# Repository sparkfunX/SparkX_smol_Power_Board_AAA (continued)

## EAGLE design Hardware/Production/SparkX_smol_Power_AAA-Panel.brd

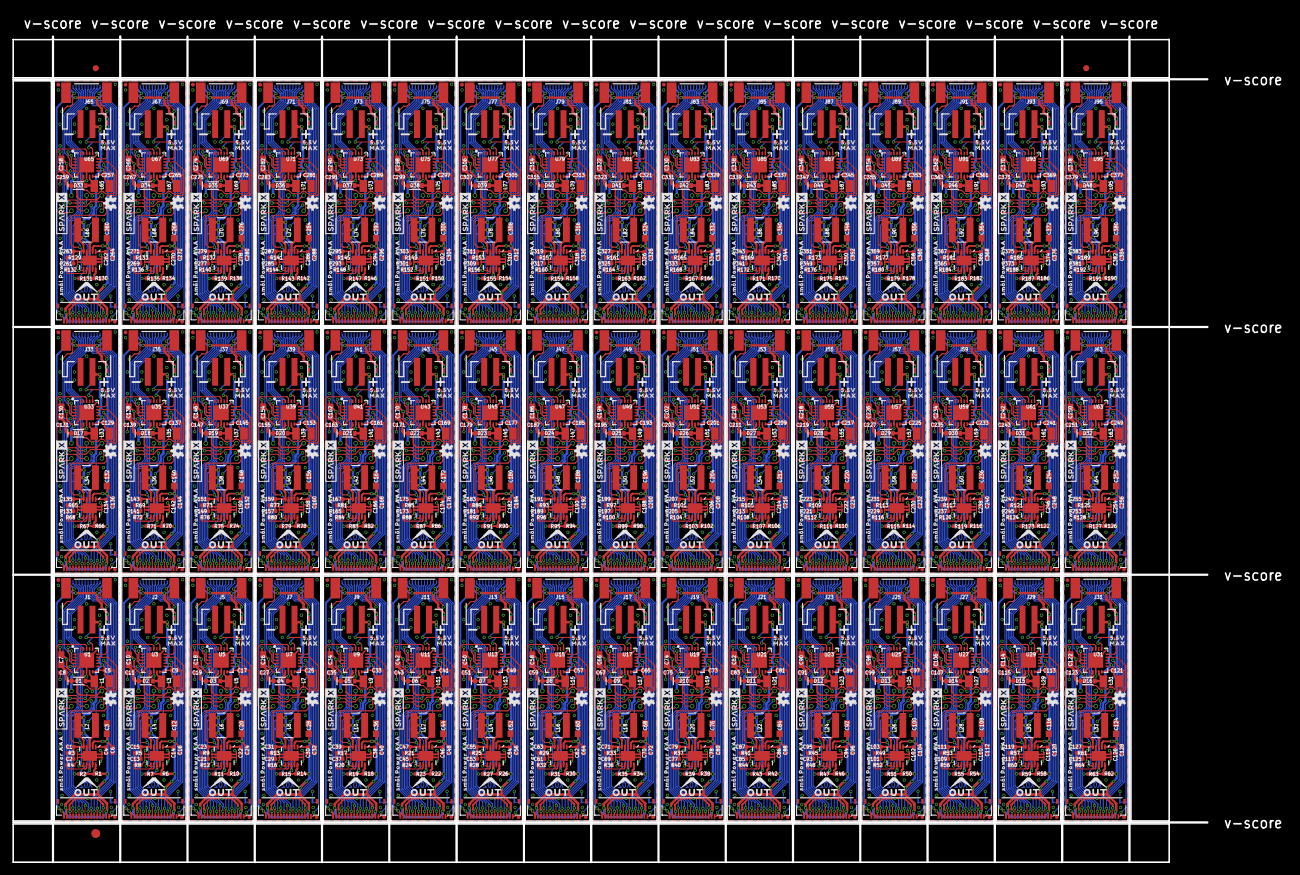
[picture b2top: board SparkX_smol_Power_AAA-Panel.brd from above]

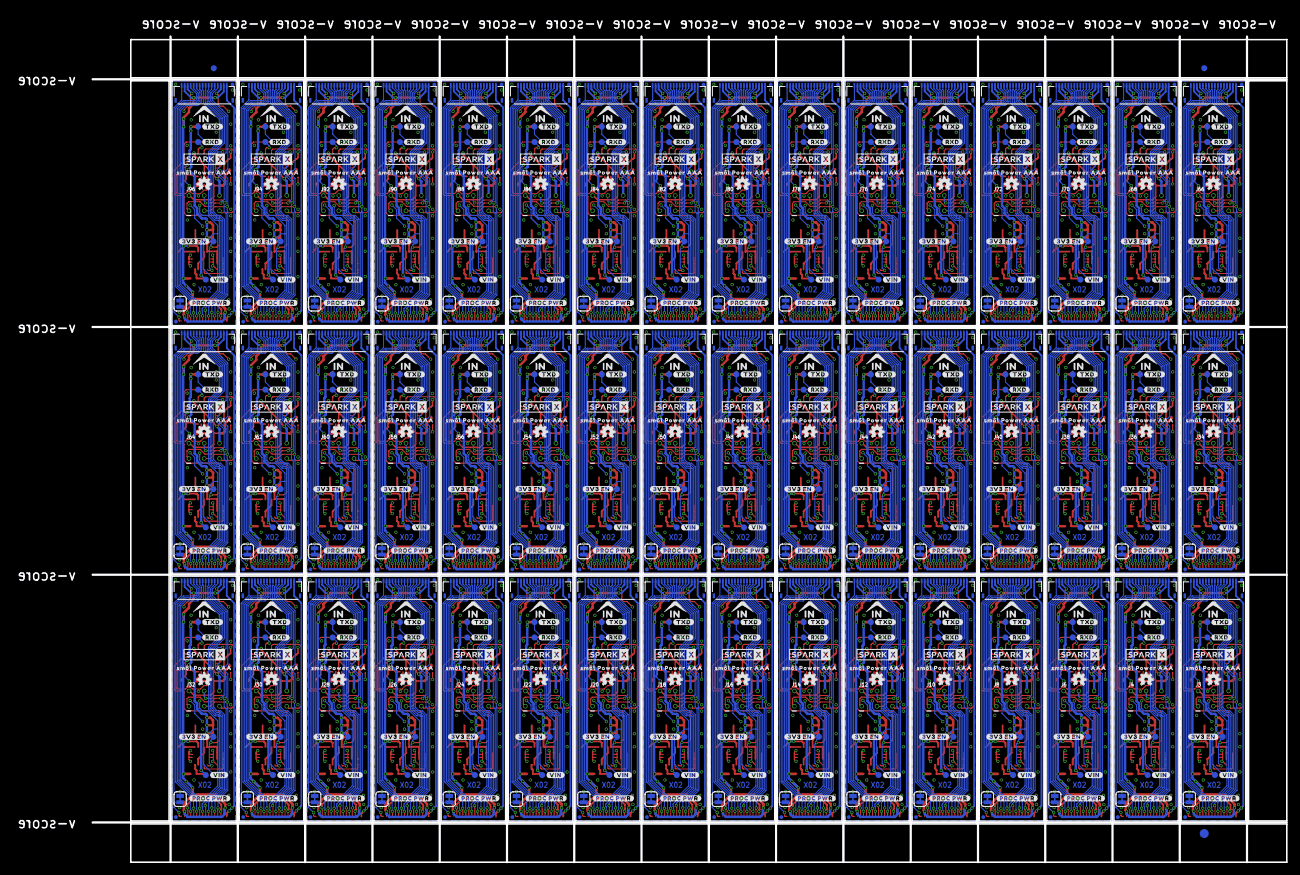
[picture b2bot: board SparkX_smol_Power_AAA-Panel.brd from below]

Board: 2 copper layers, 198.4 x 137.2 mm, 2262 parts (915 on the bottom side), 1248 nets.

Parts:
3V3_EN, 3V3_EN1, 3V3_EN2, 3V3_EN3, 3V3_EN4, 3V3_EN5, 3V3_EN6, 3V3_EN7, 3V3_EN8, 3V3_EN9, 3V3_EN10, 3V3_EN11, 3V3_EN12, 3V3_EN13, 3V3_EN14, 3V3_EN15, 3V3_EN16, 3V3_EN17, 3V3_EN18, 3V3_EN19, 3V3_EN20, 3V3_EN21, 3V3_EN22, 3V3_EN23, 3V3_EN24, 3V3_EN25, 3V3_EN26, 3V3_EN27, 3V3_EN28, 3V3_EN29, 3V3_EN30, 3V3_EN31, 3V3_EN32, 3V3_EN33, 3V3_EN34, 3V3_EN35, 3V3_EN36, 3V3_EN37, 3V3_EN38, 3V3_EN39, 3V3_EN40, 3V3_EN41, 3V3_EN42, 3V3_EN43, 3V3_EN44, 3V3_EN45, 3V3_EN46, 3V3_EN47: TEST-POINT3X4; PAD.03X.04
C1, C15, C23, C31, C39, C47, C55, C63, C71, C79, C87, C95, C103, C111, C119, C127, C135, C143, C151, C159, C167, C175, C183, C191, C199, C207, C215, C223, C231, C239, C247, C255, C263, C271, C279, C287, C295, C303, C311, C319, C327, C335, C343, C351, C359, C367, C375, C383: 10uF; 0402-TIGHT
C2, C4, C6, C8, C11, C13, C14, C16, C19, C21, C22, C24, C27, C29, C30, C32, C35, C37, C38, C40, C43, C45, C46, C48, C51, C53, C54, C56, C59, C61, C62, C64, C67, C69, C70, C72, C75, C77, C78, C80, C83, C85, C86, C88, C91, C93, C94, C96, C99, C101, C102, C104, C107, C109, C110, C112, C115, C117, C118, C120, C123, C125, C126, C128, C131, C133, C134, C136, C139, C141, C142, C144, C147, C149, C150, C152, C155, C157, C158, C160, C163, C165, C166, C168, C171, C173, C174, C176, C179, C181, C182, C184, C187, C189, C190, C192, C195, C197, C198, C200, C203, C205, C206, C208, C211, C213, C214, C216, C219, C221, C222, C224, C227, C229, C230, C232, C235, C237, C238, C240, C243, C245, C246, C248, C251, C253, C254, C256, C259, C261, C262, C264, C267, C269, C270, C272, C275, C277, C278, C280, C283, C285, C286, C288, C291, C293, C294, C296, C299, C301, C302, C304, C307, C309, C310, C312, C315, C317, C318, C320, C323, C325, C326, C328, C331, C333, C334, C336, C339, C341, C342, C344, C347, C349, C350, C352, C355, C357, C358, C360, C363, C365, C366, C368, C371, C373, C374, C376, C379, C381, C382, C384: 0.1uF; 0402-TIGHT
C3, C7, C10, C12, C18, C20, C26, C28, C34, C36, C42, C44, C50, C52, C58, C60, C66, C68, C74, C76, C82, C84, C90, C92, C98, C100, C106, C108, C114, C116, C122, C124, C130, C132, C138, C140, C146, C148, C154, C156, C162, C164, C170, C172, C178, C180, C186, C188, C194, C196, C202, C204, C210, C212, C218, C220, C226, C228, C234, C236, C242, C244, C250, C252, C258, C260, C266, C268, C274, C276, C282, C284, C290, C292, C298, C300, C306, C308, C314, C316, C322, C324, C330, C332, C338, C340, C346, C348, C354, C356, C362, C364, C370, C372, C378, C380: 22uF; 0603
C5, C9, C17, C25, C33, C41, C49, C57, C65, C73, C81, C89, C97, C105, C113, C121, C129, C137, C145, C153, C161, C169, C177, C185, C193, C201, C209, C217, C225, C233, C241, C249, C257, C265, C273, C281, C289, C297, C305, C313, C321, C329, C337, C345, C353, C361, C369, C377: 4.7uF; 0402-TIGHT
D1, D2, D3, D4, D5, D6, D7, D8, D9, D10, D11, D12, D13, D14, D15, D16, D17, D18, D19, D20, D21, D22, D23, D24, D25, D26, D27, D28, D29, D30, D31, D32, D33, D34, D35, D36, D37, D38, D39, D40, D41, D42, D43, D44, D45, D46, D47, D48: 1A/23V/620mV; SOD-323
E$1, E$2, E$3, E$4: FIDUCIAL-1X2
E$5, E$6: FIDUCIAL-1.5X3
FD1, FD2, FD3, FD4, FD5, FD6, FD7, FD8, FD9, FD10, FD11, FD12, FD13, FD14, FD15, FD16, FD17, FD18, FD19, FD20, FD21, FD22, FD23, FD24, FD25, FD26, FD27, FD28, FD29, FD30, FD31, FD32, FD33, FD34, FD35, FD36, FD37, FD38, FD39, FD40, FD41, FD42, FD43, FD44, FD45, FD46, FD47, FD48, FD49, FD50, FD51, FD52, FD53, FD54, FD55, FD56, FD57, FD58, FD59, FD60, FD61, FD62, FD63, FD64, FD65, FD66, FD67, FD68, FD69, FD70, FD71, FD72, FD73, FD74, FD75, FD76, FD77, FD78, FD79, FD80, FD81, FD82, FD83, FD84, FD85, FD86, FD87, FD88, FD89, FD90, FD91, FD92, FD93, FD94, FD95, FD96, FD97, FD98, FD99, FD100, FD101, FD102, FD103, FD104, FD105, FD106, FD107, FD108, FD109, FD110, FD111, FD112, FD113, FD114, FD115, FD116, FD117, FD118, FD119, FD120, FD121, FD122, FD123, FD124, FD125, FD126, FD127, FD128, FD129, FD130, FD131, FD132, FD133, FD134, FD135, FD136, FD137, FD138, FD139, FD140, FD141, FD142, FD143, FD144, FD145, FD146, FD147, FD148, FD149, FD150, FD151, FD152, FD153, FD154, FD155, FD156, FD157, FD158, FD159, FD160, FD161, FD162, FD163, FD164, FD165, FD166, FD167, FD168, FD169, FD170, FD171, FD172, FD173, FD174, FD175, FD176, FD177, FD178, FD179, FD180, FD181, FD182, FD183, FD184, FD185, FD186, FD187, FD188, FD189, FD190, FD191, FD192: FIDUCIALUFIDUCIAL; FIDUCIAL-MICRO
IN, IN1, IN2, IN3, IN4, IN5, IN6, IN7, IN8, IN9, IN10, IN11, IN12, IN13, IN14, IN15, IN16, IN17, IN18, IN19, IN20, IN21, IN22, IN23, IN24, IN25, IN26, IN27, IN28, IN29, IN30, IN31, IN32, IN33, IN34, IN35, IN36, IN37, IN38, IN39, IN40, IN41, IN42, IN43, IN44, IN45, IN46, IN47: FPC_16_0.5MM
J1, J2, J5, J7, J9, J11, J13, J15, J17, J19, J21, J23, J25, J27, J29, J31, J33, J35, J37, J39, J41, J43, J45, J47, J49, J51, J53, J55, J57, J59, J61, J63, J65, J67, J69, J71, J73, J75, J77, J79, J81, J83, J85, J87, J89, J91, J93, J95: JST-2-SMD
J3, J4, J6, J8, J10, J12, J14, J16, J18, J20, J22, J24, J26, J28, J30, J32, J34, J36, J38, J40, J42, J44, J46, J48, J50, J52, J54, J56, J58, J60, J62, J64, J66, J68, J70, J72, J74, J76, J78, J80, J82, J84, J86, J88, J90, J92, J94, J96: AVR_SPI_PROG_3X2TESTPOINTS; 2X3_TEST_POINTS
L1, L3, L5, L7, L9, L11, L13, L15, L17, L19, L21, L23, L25, L27, L29, L31, L33, L35, L37, L39, L41, L43, L45, L47, L49, L51, L53, L55, L57, L59, L61, L63, L65, L67, L69, L71, L73, L75, L77, L79, L81, L83, L85, L87, L89, L91, L93, L95: 15uH; INDUCTOR_LQH32
L2, L4, L6, L8, L10, L12, L14, L16, L18, L20, L22, L24, L26, L28, L30, L32, L34, L36, L38, L40, L42, L44, L46, L48, L50, L52, L54, L56, L58, L60, L62, L64, L66, L68, L70, L72, L74, L76, L78, L80, L82, L84, L86, L88, L90, L92, L94, L96: 4.7μH; INDUCTOR_4X4MM
LOGO1, LOGO2, LOGO3, LOGO4, LOGO5, LOGO6, LOGO7, LOGO8, LOGO9, LOGO10, LOGO11, LOGO12, LOGO13, LOGO14, LOGO15, LOGO16, LOGO17, LOGO18, LOGO19, LOGO20, LOGO21, LOGO22, LOGO23, LOGO24, LOGO25, LOGO26, LOGO27, LOGO28, LOGO29, LOGO30, LOGO31, LOGO32, LOGO33, LOGO34, LOGO35, LOGO36, LOGO37, LOGO38, LOGO39, LOGO40, LOGO41, LOGO42, LOGO43, LOGO44, LOGO45, LOGO46, LOGO47, LOGO48, LOGO49, LOGO50, LOGO51, LOGO52, LOGO53, LOGO54, LOGO55, LOGO56, LOGO57, LOGO58, LOGO59, LOGO60, LOGO61, LOGO62, LOGO63, LOGO64, LOGO65, LOGO66, LOGO67, LOGO68, LOGO69, LOGO70, LOGO71, LOGO72, LOGO73, LOGO74, LOGO75, LOGO76, LOGO77, LOGO78, LOGO79, LOGO80, LOGO81, LOGO82, LOGO83, LOGO84, LOGO85, LOGO86, LOGO87, LOGO88, LOGO89, LOGO90, LOGO91, LOGO92, LOGO93, LOGO94, LOGO95, LOGO96: OSHW-LOGOMINI; OSHW-LOGO-MINI
OUT, OUT1, OUT2, OUT3, OUT4, OUT5, OUT6, OUT7, OUT8, OUT9, OUT10, OUT11, OUT12, OUT13, OUT14, OUT15, OUT16, OUT17, OUT18, OUT19, OUT20, OUT21, OUT22, OUT23, OUT24, OUT25, OUT26, OUT27, OUT28, OUT29, OUT30, OUT31, OUT32, OUT33, OUT34, OUT35, OUT36, OUT37, OUT38, OUT39, OUT40, OUT41, OUT42, OUT43, OUT44, OUT45, OUT46, OUT47: FPC_16_0.5MM
PROC_PWR_EN, PROC_PWR_EN1, PROC_PWR_EN2, PROC_PWR_EN3, PROC_PWR_EN4, PROC_PWR_EN5, PROC_PWR_EN6, PROC_PWR_EN7, PROC_PWR_EN8, PROC_PWR_EN9, PROC_PWR_EN10, PROC_PWR_EN11, PROC_PWR_EN12, PROC_PWR_EN13, PROC_PWR_EN14, PROC_PWR_EN15, PROC_PWR_EN16, PROC_PWR_EN17, PROC_PWR_EN18, PROC_PWR_EN19, PROC_PWR_EN20, PROC_PWR_EN21, PROC_PWR_EN22, PROC_PWR_EN23, PROC_PWR_EN24, PROC_PWR_EN25, PROC_PWR_EN26, PROC_PWR_EN27, PROC_PWR_EN28, PROC_PWR_EN29, PROC_PWR_EN30, PROC_PWR_EN31, PROC_PWR_EN32, PROC_PWR_EN33, PROC_PWR_EN34, PROC_PWR_EN35, PROC_PWR_EN36, PROC_PWR_EN37, PROC_PWR_EN38, PROC_PWR_EN39, PROC_PWR_EN40, PROC_PWR_EN41, PROC_PWR_EN42, PROC_PWR_EN43, PROC_PWR_EN44, PROC_PWR_EN45, PROC_PWR_EN46, PROC_PWR_EN47: JUMPER-SMT_2_NC_TRACE_SILK; SMT-JUMPER_2_NC_TRACE_SILK
R1, R6, R10, R14, R18, R22, R26, R30, R34, R38, R42, R46, R50, R54, R58, R62, R66, R70, R74, R78, R82, R86, R90, R94, R98, R102, R106, R110, R114, R118, R122, R126, R130, R134, R138, R142, R146, R150, R154, R158, R162, R166, R170, R174, R178, R182, R186, R190: 1M; 0402-TIGHT
R2, R7, R11, R15, R19, R23, R27, R31, R35, R39, R43, R47, R51, R55, R59, R63, R67, R71, R75, R79, R83, R87, R91, R95, R99, R103, R107, R111, R115, R119, R123, R127, R131, R135, R139, R143, R147, R151, R155, R159, R163, R167, R171, R175, R179, R183, R187, R191: 180k; 0402-TIGHT
R3, R5, R9, R13, R17, R21, R25, R29, R33, R37, R41, R45, R49, R53, R57, R61, R65, R69, R73, R77, R81, R85, R89, R93, R97, R101, R105, R109, R113, R117, R121, R125, R129, R133, R137, R141, R145, R149, R153, R157, R161, R165, R169, R173, R177, R181, R185, R189: 453k; 0402-TIGHT
R4, R8, R12, R16, R20, R24, R28, R32, R36, R40, R44, R48, R52, R56, R60, R64, R68, R72, R76, R80, R84, R88, R92, R96, R100, R104, R108, R112, R116, R120, R124, R128, R132, R136, R140, R144, R148, R152, R156, R160, R164, R168, R172, R176, R180, R184, R188, R192: 150K; 0402-TIGHT
RXD, RXD1, RXD2, RXD3, RXD4, RXD5, RXD6, RXD7, RXD8, RXD9, RXD10, RXD11, RXD12, RXD13, RXD14, RXD15, RXD16, RXD17, RXD18, RXD19, RXD20, RXD21, RXD22, RXD23, RXD24, RXD25, RXD26, RXD27, RXD28, RXD29, RXD30, RXD31, RXD32, RXD33, RXD34, RXD35, RXD36, RXD37, RXD38, RXD39, RXD40, RXD41, RXD42, RXD43, RXD44, RXD45, RXD46, RXD47: TEST-POINT3X4; PAD.03X.04
TXD, TXD1, TXD2, TXD3, TXD4, TXD5, TXD6, TXD7, TXD8, TXD9, TXD10, TXD11, TXD12, TXD13, TXD14, TXD15, TXD16, TXD17, TXD18, TXD19, TXD20, TXD21, TXD22, TXD23, TXD24, TXD25, TXD26, TXD27, TXD28, TXD29, TXD30, TXD31, TXD32, TXD33, TXD34, TXD35, TXD36, TXD37, TXD38, TXD39, TXD40, TXD41, TXD42, TXD43, TXD44, TXD45, TXD46, TXD47: TEST-POINT3X4; PAD.03X.04
U1, U3, U5, U7, U9, U11, U13, U15, U17, U19, U21, U23, U25, U27, U29, U31, U33, U35, U37, U39, U41, U43, U45, U47, U49, U51, U53, U55, U57, U59, U61, U63, U65, U67, U69, U71, U73, U75, U77, U79, U81, U83, U85, U87, U89, U91, U93, U95: ATTINY43_QFN20; QFN20_20M1
U2, U4, U6, U8, U10, U12, U14, U16, U18, U20, U22, U24, U26, U28, U30, U32, U34, U36, U38, U40, U42, U44, U46, U48, U50, U52, U54, U56, U58, U60, U62, U64, U66, U68, U70, U72, U74, U76, U78, U80, U82, U84, U86, U88, U90, U92, U94, U96: TPS61200; QFN-10_PAD
U$1, U$15, U$16, U$20, U$31, U$32, U$46, U$47, U$61, U$62, U$76, U$77, U$91, U$92, U$106, U$107, U$121, U$122, U$136, U$137, U$151, U$152, U$166, U$167, U$181, U$182, U$196, U$197, U$211, U$212, U$226, U$227, U$241, U$242, U$256, U$257, U$271, U$272, U$286, U$287, U$301, U$302, U$316, U$317, U$331, U$332, U$346, U$347, U$361, U$362, U$376, U$377, U$391, U$392, U$406, U$407, U$421, U$422, U$436, U$437, U$451, U$452, U$466, U$467, U$481, U$482, U$496, U$497, U$511, U$512, U$526, U$527, U$541, U$542, U$556, U$557, U$571, U$572, U$586, U$587, U$601, U$602, U$616, U$617, U$631, U$632, U$646, U$647, U$661, U$662, U$676, U$677, U$691, U$692, U$706, U$707: SPARKX-LOGO3; SPARKX-SMALL
U$2, U$8, U$25, U$26, U$40, U$41, U$55, U$56, U$70, U$71, U$85, U$86, U$100, U$101, U$115, U$116, U$130, U$131, U$145, U$146, U$160, U$161, U$175, U$176, U$190, U$191, U$205, U$206, U$220, U$221, U$235, U$236, U$250, U$251, U$265, U$266, U$280, U$281, U$295, U$296, U$310, U$311, U$325, U$326, U$340, U$341, U$355, U$356, U$370, U$371, U$385, U$386, U$400, U$401, U$415, U$416, U$430, U$431, U$445, U$446, U$460, U$461, U$475, U$476, U$490, U$491, U$505, U$506, U$520, U$521, U$535, U$536, U$550, U$551, U$565, U$566, U$580, U$581, U$595, U$596, U$610, U$611, U$625, U$626, U$640, U$641, U$655, U$656, U$670, U$671, U$685, U$686, U$700, U$701, U$715, U$716: SM�L_POWER_AAA0
U$3, U$27, U$42, U$57, U$72, U$87, U$102, U$117, U$132, U$147, U$162, U$177, U$192, U$207, U$222, U$237, U$252, U$267, U$282, U$297, U$312, U$327, U$342, U$357, U$372, U$387, U$402, U$417, U$432, U$447, U$462, U$477, U$492, U$507, U$522, U$537, U$552, U$567, U$582, U$597, U$612, U$627, U$642, U$657, U$672, U$687, U$702, U$717: OUT0
U$4, U$21, U$36, U$51, U$66, U$81, U$96, U$111, U$126, U$141, U$156, U$171, U$186, U$201, U$216, U$231, U$246, U$261, U$276, U$291, U$306, U$321, U$336, U$351, U$366, U$381, U$396, U$411, U$426, U$441, U$456, U$471, U$486, U$501, U$516, U$531, U$546, U$561, U$576, U$591, U$606, U$621, U$636, U$651, U$666, U$681, U$696, U$711: #TXD#0
U$5, U$17, U$33, U$48, U$63, U$78, U$93, U$108, U$123, U$138, U$153, U$168, U$183, U$198, U$213, U$228, U$243, U$258, U$273, U$288, U$303, U$318, U$333, U$348, U$363, U$378, U$393, U$408, U$423, U$438, U$453, U$468, U$483, U$498, U$513, U$528, U$543, U$558, U$573, U$588, U$603, U$618, U$633, U$648, U$663, U$678, U$693, U$708: #VIN#0
U$6, U$18, U$34, U$49, U$64, U$79, U$94, U$109, U$124, U$139, U$154, U$169, U$184, U$199, U$214, U$229, U$244, U$259, U$274, U$289, U$304, U$319, U$334, U$349, U$364, U$379, U$394, U$409, U$424, U$439, U$454, U$469, U$484, U$499, U$514, U$529, U$544, U$559, U$574, U$589, U$604, U$619, U$634, U$649, U$664, U$679, U$694, U$709: #3V3_EN#0
U$7, U$19, U$35, U$50, U$65, U$80, U$95, U$110, U$125, U$140, U$155, U$170, U$185, U$200, U$215, U$230, U$245, U$260, U$275, U$290, U$305, U$320, U$335, U$350, U$365, U$380, U$395, U$410, U$425, U$440, U$455, U$470, U$485, U$500, U$515, U$530, U$545, U$560, U$575, U$590, U$605, U$620, U$635, U$650, U$665, U$680, U$695, U$710: #PROC_PWR#0
U$9, U$22, U$37, U$52, U$67, U$82, U$97, U$112, U$127, U$142, U$157, U$172, U$187, U$202, U$217, U$232, U$247, U$262, U$277, U$292, U$307, U$322, U$337, U$352, U$367, U$382, U$397, U$412, U$427, U$442, U$457, U$472, U$487, U$502, U$517, U$532, U$547, U$562, U$577, U$592, U$607, U$622, U$637, U$652, U$667, U$682, U$697, U$712: #RXD#0
U$10, U$23, U$38, U$53, U$68, U$83, U$98, U$113, U$128, U$143, U$158, U$173, U$188, U$203, U$218, U$233, U$248, U$263, U$278, U$293, U$308, U$323, U$338, U$353, U$368, U$383, U$398, U$413, U$428, U$443, U$458, U$473, U$488, U$503, U$518, U$533, U$548, U$563, U$578, U$593, U$608, U$623, U$638, U$653, U$668, U$683, U$698, U$713: 5#5V0
U$11, U$24, U$39, U$54, U$69, U$84, U$99, U$114, U$129, U$144, U$159, U$174, U$189, U$204, U$219, U$234, U$249, U$264, U$279, U$294, U$309, U$324, U$339, U$354, U$369, U$384, U$399, U$414, U$429, U$444, U$459, U$474, U$489, U$504, U$519, U$534, U$549, U$564, U$579, U$594, U$609, U$624, U$639, U$654, U$669, U$684, U$699, U$714: MAX0
U$12, U$28, U$43, U$58, U$73, U$88, U$103, U$118, U$133, U$148, U$163, U$178, U$193, U$208, U$223, U$238, U$253, U$268, U$283, U$298, U$313, U$328, U$343, U$358, U$373, U$388, U$403, U$418, U$433, U$448, U$463, U$478, U$493, U$508, U$523, U$538, U$553, U$568, U$583, U$598, U$613, U$628, U$643, U$658, U$673, U$688, U$703, U$718: IN0
U$13, U$14, U$29, U$30, U$44, U$45, U$59, U$60, U$74, U$75, U$89, U$90, U$104, U$105, U$119, U$120, U$134, U$135, U$149, U$150, U$164, U$165, U$179, U$180, U$194, U$195, U$209, U$210, U$224, U$225, U$239, U$240, U$254, U$255, U$269, U$270, U$284, U$285, U$299, U$300, U$314, U$315, U$329, U$330, U$344, U$345, U$359, U$360, U$374, U$375, U$389, U$390, U$404, U$405, U$419, U$420, U$434, U$435, U$449, U$450, U$464, U$465, U$479, U$480, U$494, U$495, U$509, U$510, U$524, U$525, U$539, U$540, U$554, U$555, U$569, U$570, U$584, U$585, U$599, U$600, U$614, U$615, U$629, U$630, U$644, U$645, U$659, U$660, U$674, U$675, U$689, U$690, U$704, U$705, U$719, U$720: SMOL_LOGOSMALL; SMOL_SMALL
VIN, VIN1, VIN2, VIN3, VIN4, VIN5, VIN6, VIN7, VIN8, VIN9, VIN10, VIN11, VIN12, VIN13, VIN14, VIN15, VIN16, VIN17, VIN18, VIN19, VIN20, VIN21, VIN22, VIN23, VIN24, VIN25, VIN26, VIN27, VIN28, VIN29, VIN30, VIN31, VIN32, VIN33, VIN34, VIN35, VIN36, VIN37, VIN38, VIN39, VIN40, VIN41, VIN42, VIN43, VIN44, VIN45, VIN46, VIN47: TEST-POINT3X4; PAD.03X.04

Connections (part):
3.3V: C3.1, C6.1, IN.2, IN.15, OUT.2, OUT.15, R1.2, U2.2
3.3V1: C12.1, C16.1, IN1.2, IN1.15, OUT1.2, OUT1.15, R6.2, U4.2
3.3V2: C20.1, C24.1, IN2.2, IN2.15, OUT2.2, OUT2.15, R10.2, U6.2
3.3V3: C28.1, C32.1, IN3.2, IN3.15, OUT3.2, OUT3.15, R14.2, U8.2
3.3V4: C36.1, C40.1, IN4.2, IN4.15, OUT4.2, OUT4.15, R18.2, U10.2
3.3V5: C44.1, C48.1, IN5.2, IN5.15, OUT5.2, OUT5.15, R22.2, U12.2
3.3V6: C52.1, C56.1, IN6.2, IN6.15, OUT6.2, OUT6.15, R26.2, U14.2
3.3V7: C60.1, C64.1, IN7.2, IN7.15, OUT7.2, OUT7.15, R30.2, U16.2
3.3V8: C68.1, C72.1, IN8.2, IN8.15, OUT8.2, OUT8.15, R34.2, U18.2
3.3V9: C76.1, C80.1, IN9.2, IN9.15, OUT9.2, OUT9.15, R38.2, U20.2
3.3V10: C84.1, C88.1, IN10.2, IN10.15, OUT10.2, OUT10.15, R42.2, U22.2
3.3V11: C92.1, C96.1, IN11.2, IN11.15, OUT11.2, OUT11.15, R46.2, U24.2
3.3V12: C100.1, C104.1, IN12.2, IN12.15, OUT12.2, OUT12.15, R50.2, U26.2
3.3V13: C108.1, C112.1, IN13.2, IN13.15, OUT13.2, OUT13.15, R54.2, U28.2
3.3V14: C116.1, C120.1, IN14.2, IN14.15, OUT14.2, OUT14.15, R58.2, U30.2
3.3V15: C124.1, C128.1, IN15.2, IN15.15, OUT15.2, OUT15.15, R62.2, U32.2
3.3V16: C132.1, C136.1, IN16.2, IN16.15, OUT16.2, OUT16.15, R66.2, U34.2
3.3V17: C140.1, C144.1, IN17.2, IN17.15, OUT17.2, OUT17.15, R70.2, U36.2
3.3V18: C148.1, C152.1, IN18.2, IN18.15, OUT18.2, OUT18.15, R74.2, U38.2
3.3V19: C156.1, C160.1, IN19.2, IN19.15, OUT19.2, OUT19.15, R78.2, U40.2
3.3V20: C164.1, C168.1, IN20.2, IN20.15, OUT20.2, OUT20.15, R82.2, U42.2
3.3V21: C172.1, C176.1, IN21.2, IN21.15, OUT21.2, OUT21.15, R86.2, U44.2
3.3V22: C180.1, C184.1, IN22.2, IN22.15, OUT22.2, OUT22.15, R90.2, U46.2
3.3V23: C188.1, C192.1, IN23.2, IN23.15, OUT23.2, OUT23.15, R94.2, U48.2
3.3V24: C196.1, C200.1, IN24.2, IN24.15, OUT24.2, OUT24.15, R98.2, U50.2
3.3V25: C204.1, C208.1, IN25.2, IN25.15, OUT25.2, OUT25.15, R102.2, U52.2
3.3V26: C212.1, C216.1, IN26.2, IN26.15, OUT26.2, OUT26.15, R106.2, U54.2
3.3V27: C220.1, C224.1, IN27.2, IN27.15, OUT27.2, OUT27.15, R110.2, U56.2
3.3V28: C228.1, C232.1, IN28.2, IN28.15, OUT28.2, OUT28.15, R114.2, U58.2
3.3V29: C236.1, C240.1, IN29.2, IN29.15, OUT29.2, OUT29.15, R118.2, U60.2
3.3V30: C244.1, C248.1, IN30.2, IN30.15, OUT30.2, OUT30.15, R122.2, U62.2
3.3V31: C252.1, C256.1, IN31.2, IN31.15, OUT31.2, OUT31.15, R126.2, U64.2
3.3V32: C260.1, C264.1, IN32.2, IN32.15, OUT32.2, OUT32.15, R130.2, U66.2
3.3V33: C268.1, C272.1, IN33.2, IN33.15, OUT33.2, OUT33.15, R134.2, U68.2
3.3V34: C276.1, C280.1, IN34.2, IN34.15, OUT34.2, OUT34.15, R138.2, U70.2
3.3V35: C284.1, C288.1, IN35.2, IN35.15, OUT35.2, OUT35.15, R142.2, U72.2
3.3V36: C292.1, C296.1, IN36.2, IN36.15, OUT36.2, OUT36.15, R146.2, U74.2
3.3V37: C300.1, C304.1, IN37.2, IN37.15, OUT37.2, OUT37.15, R150.2, U76.2
3.3V38: C308.1, C312.1, IN38.2, IN38.15, OUT38.2, OUT38.15, R154.2, U78.2
3.3V39: C316.1, C320.1, IN39.2, IN39.15, OUT39.2, OUT39.15, R158.2, U80.2
3.3V40: C324.1, C328.1, IN40.2, IN40.15, OUT40.2, OUT40.15, R162.2, U82.2
3.3V41: C332.1, C336.1, IN41.2, IN41.15, OUT41.2, OUT41.15, R166.2, U84.2
3.3V42: C340.1, C344.1, IN42.2, IN42.15, OUT42.2, OUT42.15, R170.2, U86.2
3.3V43: C348.1, C352.1, IN43.2, IN43.15, OUT43.2, OUT43.15, R174.2, U88.2
3.3V44: C356.1, C360.1, IN44.2, IN44.15, OUT44.2, OUT44.15, R178.2, U90.2
3.3V45: C364.1, C368.1, IN45.2, IN45.15, OUT45.2, OUT45.15, R182.2, U92.2
3.3V46: C372.1, C376.1, IN46.2, IN46.15, OUT46.2, OUT46.15, R186.2, U94.2
3.3V47: C380.1, C384.1, IN47.2, IN47.15, OUT47.2, OUT47.15, R190.2, U96.2
3V3_EN: 3V3_EN.1, U1.14, U2.6
3V3_EN1: 3V3_EN1.1, U3.14, U4.6
3V3_EN2: 3V3_EN2.1, U5.14, U6.6
3V3_EN3: 3V3_EN3.1, U7.14, U8.6
3V3_EN4: 3V3_EN4.1, U9.14, U10.6
3V3_EN5: 3V3_EN5.1, U11.14, U12.6
3V3_EN6: 3V3_EN6.1, U13.14, U14.6
3V3_EN7: 3V3_EN7.1, U15.14, U16.6
3V3_EN8: 3V3_EN8.1, U17.14, U18.6
3V3_EN9: 3V3_EN9.1, U19.14, U20.6
3V3_EN10: 3V3_EN10.1, U21.14, U22.6
3V3_EN11: 3V3_EN11.1, U23.14, U24.6
3V3_EN12: 3V3_EN12.1, U25.14, U26.6
3V3_EN13: 3V3_EN13.1, U27.14, U28.6
3V3_EN14: 3V3_EN14.1, U29.14, U30.6
3V3_EN15: 3V3_EN15.1, U31.14, U32.6
3V3_EN16: 3V3_EN16.1, U33.14, U34.6
3V3_EN17: 3V3_EN17.1, U35.14, U36.6
3V3_EN18: 3V3_EN18.1, U37.14, U38.6
3V3_EN19: 3V3_EN19.1, U39.14, U40.6
3V3_EN20: 3V3_EN20.1, U41.14, U42.6
3V3_EN21: 3V3_EN21.1, U43.14, U44.6
3V3_EN22: 3V3_EN22.1, U45.14, U46.6
3V3_EN23: 3V3_EN23.1, U47.14, U48.6
3V3_EN24: 3V3_EN24.1, U49.14, U50.6
3V3_EN25: 3V3_EN25.1, U51.14, U52.6
3V3_EN26: 3V3_EN26.1, U53.14, U54.6
3V3_EN27: 3V3_EN27.1, U55.14, U56.6
3V3_EN28: 3V3_EN28.1, U57.14, U58.6
3V3_EN29: 3V3_EN29.1, U59.14, U60.6
3V3_EN30: 3V3_EN30.1, U61.14, U62.6
3V3_EN31: 3V3_EN31.1, U63.14, U64.6
3V3_EN32: 3V3_EN32.1, U65.14, U66.6
3V3_EN33: 3V3_EN33.1, U67.14, U68.6
3V3_EN34: 3V3_EN34.1, U69.14, U70.6
3V3_EN35: 3V3_EN35.1, U71.14, U72.6
3V3_EN36: 3V3_EN36.1, U73.14, U74.6
3V3_EN37: 3V3_EN37.1, U75.14, U76.6
3V3_EN38: 3V3_EN38.1, U77.14, U78.6
3V3_EN39: 3V3_EN39.1, U79.14, U80.6
3V3_EN40: 3V3_EN40.1, U81.14, U82.6
3V3_EN41: 3V3_EN41.1, U83.14, U84.6
3V3_EN42: 3V3_EN42.1, U85.14, U86.6
3V3_EN43: 3V3_EN43.1, U87.14, U88.6
3V3_EN44: 3V3_EN44.1, U89.14, U90.6
3V3_EN45: 3V3_EN45.1, U91.14, U92.6
3V3_EN46: 3V3_EN46.1, U93.14, U94.6
3V3_EN47: 3V3_EN47.1, U95.14, U96.6
!RESET!: J3.5, U1.18
!RESET!1: J4.5, U3.18
!RESET!2: J6.5, U5.18
!RESET!3: J8.5, U7.18
!RESET!4: J10.5, U9.18
!RESET!5: J12.5, U11.18
!RESET!6: J14.5, U13.18
!RESET!7: J16.5, U15.18
!RESET!8: J18.5, U17.18
!RESET!9: J20.5, U19.18
!RESET!10: J22.5, U21.18
!RESET!11: J24.5, U23.18
!RESET!12: J26.5, U25.18
!RESET!13: J28.5, U27.18
!RESET!14: J30.5, U29.18
!RESET!15: J32.5, U31.18
!RESET!16: J34.5, U33.18
!RESET!17: J36.5, U35.18
!RESET!18: J38.5, U37.18
!RESET!19: J40.5, U39.18
!RESET!20: J42.5, U41.18
!RESET!21: J44.5, U43.18
!RESET!22: J46.5, U45.18
!RESET!23: J48.5, U47.18
!RESET!24: J50.5, U49.18
!RESET!25: J52.5, U51.18
!RESET!26: J54.5, U53.18
!RESET!27: J56.5, U55.18
!RESET!28: J58.5, U57.18
!RESET!29: J60.5, U59.18
!RESET!30: J62.5, U61.18
!RESET!31: J64.5, U63.18
!RESET!32: J66.5, U65.18
!RESET!33: J68.5, U67.18
!RESET!34: J70.5, U69.18
!RESET!35: J72.5, U71.18
!RESET!36: J74.5, U73.18
!RESET!37: J76.5, U75.18
!RESET!38: J78.5, U77.18
!RESET!39: J80.5, U79.18
!RESET!40: J82.5, U81.18
!RESET!41: J84.5, U83.18
!RESET!42: J86.5, U85.18
!RESET!43: J88.5, U87.18
!RESET!44: J90.5, U89.18
!RESET!45: J92.5, U91.18
!RESET!46: J94.5, U93.18
!RESET!47: J96.5, U95.18
AT_CIPO: J3.1, U1.4
AT_CIPO1: J4.1, U3.4
AT_CIPO2: J6.1, U5.4
AT_CIPO3: J8.1, U7.4
AT_CIPO4: J10.1, U9.4
AT_CIPO5: J12.1, U11.4
AT_CIPO6: J14.1, U13.4
AT_CIPO7: J16.1, U15.4
AT_CIPO8: J18.1, U17.4
AT_CIPO9: J20.1, U19.4
AT_CIPO10: J22.1, U21.4
AT_CIPO11: J24.1, U23.4
AT_CIPO12: J26.1, U25.4
AT_CIPO13: J28.1, U27.4
AT_CIPO14: J30.1, U29.4
AT_CIPO15: J32.1, U31.4
AT_CIPO16: J34.1, U33.4
AT_CIPO17: J36.1, U35.4
AT_CIPO18: J38.1, U37.4
AT_CIPO19: J40.1, U39.4
AT_CIPO20: J42.1, U41.4
AT_CIPO21: J44.1, U43.4
AT_CIPO22: J46.1, U45.4
AT_CIPO23: J48.1, U47.4
AT_CIPO24: J50.1, U49.4
AT_CIPO25: J52.1, U51.4
AT_CIPO26: J54.1, U53.4
AT_CIPO27: J56.1, U55.4
AT_CIPO28: J58.1, U57.4
AT_CIPO29: J60.1, U59.4
AT_CIPO30: J62.1, U61.4
AT_CIPO31: J64.1, U63.4
AT_CIPO32: J66.1, U65.4
AT_CIPO33: J68.1, U67.4
AT_CIPO34: J70.1, U69.4
AT_CIPO35: J72.1, U71.4
AT_CIPO36: J74.1, U73.4
AT_CIPO37: J76.1, U75.4
AT_CIPO38: J78.1, U77.4
AT_CIPO39: J80.1, U79.4
AT_CIPO40: J82.1, U81.4
AT_CIPO41: J84.1, U83.4
AT_CIPO42: J86.1, U85.4
AT_CIPO43: J88.1, U87.4
AT_CIPO44: J90.1, U89.4
AT_CIPO45: J92.1, U91.4
AT_CIPO46: J94.1, U93.4
AT_CIPO47: J96.1, U95.4
AT_VCC: C7.1, C8.1, D1.C, J3.2, U1.7
AT_VCC1: C10.1, C11.1, D2.C, J4.2, U3.7
AT_VCC2: C18.1, C19.1, D3.C, J6.2, U5.7
AT_VCC3: C26.1, C27.1, D4.C, J8.2, U7.7
AT_VCC4: C34.1, C35.1, D5.C, J10.2, U9.7
AT_VCC5: C42.1, C43.1, D6.C, J12.2, U11.7
AT_VCC6: C50.1, C51.1, D7.C, J14.2, U13.7
AT_VCC7: C58.1, C59.1, D8.C, J16.2, U15.7
AT_VCC8: C66.1, C67.1, D9.C, J18.2, U17.7
AT_VCC9: C74.1, C75.1, D10.C, J20.2, U19.7
AT_VCC10: C82.1, C83.1, D11.C, J22.2, U21.7
AT_VCC11: C90.1, C91.1, D12.C, J24.2, U23.7
AT_VCC12: C98.1, C99.1, D13.C, J26.2, U25.7
AT_VCC13: C106.1, C107.1, D14.C, J28.2, U27.7
AT_VCC14: C114.1, C115.1, D15.C, J30.2, U29.7
AT_VCC15: C122.1, C123.1, D16.C, J32.2, U31.7
AT_VCC16: C130.1, C131.1, D17.C, J34.2, U33.7
AT_VCC17: C138.1, C139.1, D18.C, J36.2, U35.7
AT_VCC18: C146.1, C147.1, D19.C, J38.2, U37.7
AT_VCC19: C154.1, C155.1, D20.C, J40.2, U39.7
AT_VCC20: C162.1, C163.1, D21.C, J42.2, U41.7
AT_VCC21: C170.1, C171.1, D22.C, J44.2, U43.7
AT_VCC22: C178.1, C179.1, D23.C, J46.2, U45.7
AT_VCC23: C186.1, C187.1, D24.C, J48.2, U47.7
AT_VCC24: C194.1, C195.1, D25.C, J50.2, U49.7
AT_VCC25: C202.1, C203.1, D26.C, J52.2, U51.7
AT_VCC26: C210.1, C211.1, D27.C, J54.2, U53.7
AT_VCC27: C218.1, C219.1, D28.C, J56.2, U55.7
AT_VCC28: C226.1, C227.1, D29.C, J58.2, U57.7
AT_VCC29: C234.1, C235.1, D30.C, J60.2, U59.7
AT_VCC30: C242.1, C243.1, D31.C, J62.2, U61.7
AT_VCC31: C250.1, C251.1, D32.C, J64.2, U63.7
AT_VCC32: C258.1, C259.1, D33.C, J66.2, U65.7
AT_VCC33: C266.1, C267.1, D34.C, J68.2, U67.7
AT_VCC34: C274.1, C275.1, D35.C, J70.2, U69.7
AT_VCC35: C282.1, C283.1, D36.C, J72.2, U71.7
AT_VCC36: C290.1, C291.1, D37.C, J74.2, U73.7
AT_VCC37: C298.1, C299.1, D38.C, J76.2, U75.7
AT_VCC38: C306.1, C307.1, D39.C, J78.2, U77.7
AT_VCC39: C314.1, C315.1, D40.C, J80.2, U79.7
AT_VCC40: C322.1, C323.1, D41.C, J82.2, U81.7
AT_VCC41: C330.1, C331.1, D42.C, J84.2, U83.7
AT_VCC42: C338.1, C339.1, D43.C, J86.2, U85.7
AT_VCC43: C346.1, C347.1, D44.C, J88.2, U87.7
AT_VCC44: C354.1, C355.1, D45.C, J90.2, U89.7
AT_VCC45: C362.1, C363.1, D46.C, J92.2, U91.7
AT_VCC46: C370.1, C371.1, D47.C, J94.2, U93.7
AT_VCC47: C378.1, C379.1, D48.C, J96.2, U95.7
CIPO: IN.6, OUT.6
CIPO1: IN1.6, OUT1.6
CIPO2: IN2.6, OUT2.6
CIPO3: IN3.6, OUT3.6
CIPO4: IN4.6, OUT4.6
CIPO5: IN5.6, OUT5.6
CIPO6: IN6.6, OUT6.6
CIPO7: IN7.6, OUT7.6
CIPO8: IN8.6, OUT8.6
CIPO9: IN9.6, OUT9.6
CIPO10: IN10.6, OUT10.6
CIPO11: IN11.6, OUT11.6
CIPO12: IN12.6, OUT12.6
CIPO13: IN13.6, OUT13.6
CIPO14: IN14.6, OUT14.6
CIPO15: IN15.6, OUT15.6
CIPO16: IN16.6, OUT16.6
CIPO17: IN17.6, OUT17.6
CIPO18: IN18.6, OUT18.6
CIPO19: IN19.6, OUT19.6
CIPO20: IN20.6, OUT20.6
CIPO21: IN21.6, OUT21.6
CIPO22: IN22.6, OUT22.6
CIPO23: IN23.6, OUT23.6
CIPO24: IN24.6, OUT24.6
CIPO25: IN25.6, OUT25.6
CIPO26: IN26.6, OUT26.6
CIPO27: IN27.6, OUT27.6
CIPO28: IN28.6, OUT28.6
CIPO29: IN29.6, OUT29.6
CIPO30: IN30.6, OUT30.6
CIPO31: IN31.6, OUT31.6
CIPO32: IN32.6, OUT32.6
CIPO33: IN33.6, OUT33.6
CIPO34: IN34.6, OUT34.6
CIPO35: IN35.6, OUT35.6
CIPO36: IN36.6, OUT36.6
CIPO37: IN37.6, OUT37.6
CIPO38: IN38.6, OUT38.6
CIPO39: IN39.6, OUT39.6
CIPO40: IN40.6, OUT40.6
CIPO41: IN41.6, OUT41.6
CIPO42: IN42.6, OUT42.6
CIPO43: IN43.6, OUT43.6
CIPO44: IN44.6, OUT44.6
CIPO45: IN45.6, OUT45.6
CIPO46: IN46.6, OUT46.6
CIPO47: IN47.6, OUT47.6
COPI: IN.5, OUT.5
COPI1: IN1.5, OUT1.5
COPI2: IN2.5, OUT2.5
COPI3: IN3.5, OUT3.5
COPI4: IN4.5, OUT4.5
COPI5: IN5.5, OUT5.5
COPI6: IN6.5, OUT6.5
COPI7: IN7.5, OUT7.5
COPI8: IN8.5, OUT8.5
COPI9: IN9.5, OUT9.5
COPI10: IN10.5, OUT10.5
COPI11: IN11.5, OUT11.5
COPI12: IN12.5, OUT12.5
COPI13: IN13.5, OUT13.5
COPI14: IN14.5, OUT14.5
COPI15: IN15.5, OUT15.5
COPI16: IN16.5, OUT16.5
COPI17: IN17.5, OUT17.5
COPI18: IN18.5, OUT18.5
COPI19: IN19.5, OUT19.5
COPI20: IN20.5, OUT20.5
COPI21: IN21.5, OUT21.5
COPI22: IN22.5, OUT22.5
COPI23: IN23.5, OUT23.5
COPI24: IN24.5, OUT24.5
COPI25: IN25.5, OUT25.5
COPI26: IN26.5, OUT26.5
COPI27: IN27.5, OUT27.5
COPI28: IN28.5, OUT28.5
COPI29: IN29.5, OUT29.5
COPI30: IN30.5, OUT30.5
COPI31: IN31.5, OUT31.5
COPI32: IN32.5, OUT32.5
COPI33: IN33.5, OUT33.5
COPI34: IN34.5, OUT34.5
COPI35: IN35.5, OUT35.5
COPI36: IN36.5, OUT36.5
COPI37: IN37.5, OUT37.5
COPI38: IN38.5, OUT38.5
COPI39: IN39.5, OUT39.5
COPI40: IN40.5, OUT40.5
COPI41: IN41.5, OUT41.5
COPI42: IN42.5, OUT42.5
COPI43: IN43.5, OUT43.5
COPI44: IN44.5, OUT44.5
COPI45: IN45.5, OUT45.5
COPI46: IN46.5, OUT46.5
COPI47: IN47.5, OUT47.5
CS0: IN.7, OUT.7
CS1: IN.8, OUT.8
CS2: IN.9, OUT.9
CS3: IN1.7, OUT1.7
CS4: IN1.8, OUT1.8
CS5: IN1.9, OUT1.9
CS6: IN2.7, OUT2.7
CS7: IN2.8, OUT2.8
CS8: IN2.9, OUT2.9
CS9: IN3.7, OUT3.7
CS10: IN3.8, OUT3.8
CS11: IN3.9, OUT3.9
CS12: IN4.7, OUT4.7
CS13: IN4.8, OUT4.8
CS14: IN4.9, OUT4.9
CS15: IN5.7, OUT5.7
CS16: IN5.8, OUT5.8
CS17: IN5.9, OUT5.9
CS18: IN6.7, OUT6.7
CS19: IN6.8, OUT6.8
CS20: IN6.9, OUT6.9
CS21: IN7.7, OUT7.7
CS22: IN7.8, OUT7.8
CS23: IN7.9, OUT7.9
CS24: IN8.7, OUT8.7
CS25: IN8.8, OUT8.8
CS26: IN8.9, OUT8.9
CS27: IN9.7, OUT9.7
CS28: IN9.8, OUT9.8
CS29: IN9.9, OUT9.9
CS30: IN10.7, OUT10.7
CS31: IN10.8, OUT10.8
CS32: IN10.9, OUT10.9
CS33: IN11.7, OUT11.7
CS34: IN11.8, OUT11.8
CS35: IN11.9, OUT11.9
CS36: IN12.7, OUT12.7
CS37: IN12.8, OUT12.8
CS38: IN12.9, OUT12.9
CS39: IN13.7, OUT13.7
CS40: IN13.8, OUT13.8
CS41: IN13.9, OUT13.9
CS42: IN14.7, OUT14.7
CS43: IN14.8, OUT14.8
CS44: IN14.9, OUT14.9
CS45: IN15.7, OUT15.7
CS46: IN15.8, OUT15.8
CS47: IN15.9, OUT15.9
CS48: IN16.7, OUT16.7
CS49: IN16.8, OUT16.8
CS50: IN16.9, OUT16.9
CS51: IN17.7, OUT17.7
CS52: IN17.8, OUT17.8
CS53: IN17.9, OUT17.9
CS54: IN18.7, OUT18.7
CS55: IN18.8, OUT18.8
CS56: IN18.9, OUT18.9
CS57: IN19.7, OUT19.7
CS58: IN19.8, OUT19.8
CS59: IN19.9, OUT19.9
CS60: IN20.7, OUT20.7
CS61: IN20.8, OUT20.8
CS62: IN20.9, OUT20.9
CS63: IN21.7, OUT21.7
CS64: IN21.8, OUT21.8
CS65: IN21.9, OUT21.9
CS66: IN22.7, OUT22.7
CS67: IN22.8, OUT22.8
CS68: IN22.9, OUT22.9
CS69: IN23.7, OUT23.7
CS70: IN23.8, OUT23.8
CS71: IN23.9, OUT23.9
CS72: IN24.7, OUT24.7
CS73: IN24.8, OUT24.8
CS74: IN24.9, OUT24.9
CS75: IN25.7, OUT25.7
CS76: IN25.8, OUT25.8
CS77: IN25.9, OUT25.9
CS78: IN26.7, OUT26.7
CS79: IN26.8, OUT26.8
CS80: IN26.9, OUT26.9
CS81: IN27.7, OUT27.7
CS82: IN27.8, OUT27.8
CS83: IN27.9, OUT27.9
CS84: IN28.7, OUT28.7
CS85: IN28.8, OUT28.8
CS86: IN28.9, OUT28.9
CS87: IN29.7, OUT29.7
CS88: IN29.8, OUT29.8
CS89: IN29.9, OUT29.9
CS90: IN30.7, OUT30.7
CS91: IN30.8, OUT30.8
CS92: IN30.9, OUT30.9
CS93: IN31.7, OUT31.7
CS94: IN31.8, OUT31.8
CS95: IN31.9, OUT31.9
CS96: IN32.7, OUT32.7
CS97: IN32.8, OUT32.8
CS98: IN32.9, OUT32.9
CS99: IN33.7, OUT33.7
CS100: IN33.8, OUT33.8
CS101: IN33.9, OUT33.9
CS102: IN34.7, OUT34.7
CS103: IN34.8, OUT34.8
CS104: IN34.9, OUT34.9
CS105: IN35.7, OUT35.7
CS106: IN35.8, OUT35.8
CS107: IN35.9, OUT35.9
CS108: IN36.7, OUT36.7
CS109: IN36.8, OUT36.8
CS110: IN36.9, OUT36.9
CS111: IN37.7, OUT37.7
CS112: IN37.8, OUT37.8
CS113: IN37.9, OUT37.9
CS114: IN38.7, OUT38.7
CS115: IN38.8, OUT38.8
CS116: IN38.9, OUT38.9
CS117: IN39.7, OUT39.7
CS118: IN39.8, OUT39.8
CS119: IN39.9, OUT39.9
CS120: IN40.7, OUT40.7
CS121: IN40.8, OUT40.8
CS122: IN40.9, OUT40.9
CS123: IN41.7, OUT41.7
CS124: IN41.8, OUT41.8
CS125: IN41.9, OUT41.9
CS126: IN42.7, OUT42.7
CS127: IN42.8, OUT42.8
CS128: IN42.9, OUT42.9
CS129: IN43.7, OUT43.7
CS130: IN43.8, OUT43.8
CS131: IN43.9, OUT43.9
CS132: IN44.7, OUT44.7
CS133: IN44.8, OUT44.8
CS134: IN44.9, OUT44.9
CS135: IN45.7, OUT45.7
CS136: IN45.8, OUT45.8
CS137: IN45.9, OUT45.9
CS138: IN46.7, OUT46.7
CS139: IN46.8, OUT46.8
CS140: IN46.9, OUT46.9
CS141: IN47.7, OUT47.7
CS142: IN47.8, OUT47.8
CS143: IN47.9, OUT47.9
FB: R1.1, R2.2, U2.10
FB1: R6.1, R7.2, U4.10
FB2: R10.1, R11.2, U6.10
FB3: R14.1, R15.2, U8.10
FB4: R18.1, R19.2, U10.10
FB5: R22.1, R23.2, U12.10
FB6: R26.1, R27.2, U14.10
FB7: R30.1, R31.2, U16.10
FB8: R34.1, R35.2, U18.10
FB9: R38.1, R39.2, U20.10
FB10: R42.1, R43.2, U22.10
FB11: R46.1, R47.2, U24.10
FB12: R50.1, R51.2, U26.10
FB13: R54.1, R55.2, U28.10
FB14: R58.1, R59.2, U30.10
FB15: R62.1, R63.2, U32.10
FB16: R66.1, R67.2, U34.10
FB17: R70.1, R71.2, U36.10
FB18: R74.1, R75.2, U38.10
FB19: R78.1, R79.2, U40.10
FB20: R82.1, R83.2, U42.10
FB21: R86.1, R87.2, U44.10
FB22: R90.1, R91.2, U46.10
FB23: R94.1, R95.2, U48.10
FB24: R98.1, R99.2, U50.10
FB25: R102.1, R103.2, U52.10
FB26: R106.1, R107.2, U54.10
FB27: R110.1, R111.2, U56.10
FB28: R114.1, R115.2, U58.10
FB29: R118.1, R119.2, U60.10
FB30: R122.1, R123.2, U62.10
FB31: R126.1, R127.2, U64.10
FB32: R130.1, R131.2, U66.10
FB33: R134.1, R135.2, U68.10
FB34: R138.1, R139.2, U70.10
FB35: R142.1, R143.2, U72.10
FB36: R146.1, R147.2, U74.10
FB37: R150.1, R151.2, U76.10
FB38: R154.1, R155.2, U78.10
FB39: R158.1, R159.2, U80.10
FB40: R162.1, R163.2, U82.10
FB41: R166.1, R167.2, U84.10
FB42: R170.1, R171.2, U86.10
FB43: R174.1, R175.2, U88.10
FB44: R178.1, R179.2, U90.10
FB45: R182.1, R183.2, U92.10
FB46: R186.1, R187.2, U94.10
FB47: R190.1, R191.2, U96.10
GND: C1.2, C3.2, C4.2, C5.2, C6.2, C7.2, C8.2, IN.3, IN.14, J1.1, J3.6, OUT.3, OUT.14, PROC_PWR_EN.2, R2.1, R4.1, U1.8, U1.PAD, U2.4, U2.9, U2.11, U2.12, U2.13, U2.14, U2.15
GND1: C9.2, C10.2, C11.2, C12.2, C14.2, C15.2, C16.2, IN1.3, IN1.14, J2.1, J4.6, OUT1.3, OUT1.14, PROC_PWR_EN1.2, R7.1, R8.1, U3.8, U3.PAD, U4.4, U4.9, U4.11, U4.12, U4.13, U4.14, U4.15
GND2: C17.2, C18.2, C19.2, C20.2, C22.2, C23.2, C24.2, IN2.3, IN2.14, J5.1, J6.6, OUT2.3, OUT2.14, PROC_PWR_EN2.2, R11.1, R12.1, U5.8, U5.PAD, U6.4, U6.9, U6.11, U6.12, U6.13, U6.14, U6.15
GND3: C25.2, C26.2, C27.2, C28.2, C30.2, C31.2, C32.2, IN3.3, IN3.14, J7.1, J8.6, OUT3.3, OUT3.14, PROC_PWR_EN3.2, R15.1, R16.1, U7.8, U7.PAD, U8.4, U8.9, U8.11, U8.12, U8.13, U8.14, U8.15
GND4: C33.2, C34.2, C35.2, C36.2, C38.2, C39.2, C40.2, IN4.3, IN4.14, J9.1, J10.6, OUT4.3, OUT4.14, PROC_PWR_EN4.2, R19.1, R20.1, U9.8, U9.PAD, U10.4, U10.9, U10.11, U10.12, U10.13, U10.14, U10.15
GND5: C41.2, C42.2, C43.2, C44.2, C46.2, C47.2, C48.2, IN5.3, IN5.14, J11.1, J12.6, OUT5.3, OUT5.14, PROC_PWR_EN5.2, R23.1, R24.1, U11.8, U11.PAD, U12.4, U12.9, U12.11, U12.12, U12.13, U12.14, U12.15
GND6: C49.2, C50.2, C51.2, C52.2, C54.2, C55.2, C56.2, IN6.3, IN6.14, J13.1, J14.6, OUT6.3, OUT6.14, PROC_PWR_EN6.2, R27.1, R28.1, U13.8, U13.PAD, U14.4, U14.9, U14.11, U14.12, U14.13, U14.14, U14.15
GND7: C57.2, C58.2, C59.2, C60.2, C62.2, C63.2, C64.2, IN7.3, IN7.14, J15.1, J16.6, OUT7.3, OUT7.14, PROC_PWR_EN7.2, R31.1, R32.1, U15.8, U15.PAD, U16.4, U16.9, U16.11, U16.12, U16.13, U16.14, U16.15
GND8: C65.2, C66.2, C67.2, C68.2, C70.2, C71.2, C72.2, IN8.3, IN8.14, J17.1, J18.6, OUT8.3, OUT8.14, PROC_PWR_EN8.2, R35.1, R36.1, U17.8, U17.PAD, U18.4, U18.9, U18.11, U18.12, U18.13, U18.14, U18.15
GND9: C73.2, C74.2, C75.2, C76.2, C78.2, C79.2, C80.2, IN9.3, IN9.14, J19.1, J20.6, OUT9.3, OUT9.14, PROC_PWR_EN9.2, R39.1, R40.1, U19.8, U19.PAD, U20.4, U20.9, U20.11, U20.12, U20.13, U20.14, U20.15
GND10: C81.2, C82.2, C83.2, C84.2, C86.2, C87.2, C88.2, IN10.3, IN10.14, J21.1, J22.6, OUT10.3, OUT10.14, PROC_PWR_EN10.2, R43.1, R44.1, U21.8, U21.PAD, U22.4, U22.9, U22.11, U22.12, U22.13, U22.14, U22.15
GND11: C89.2, C90.2, C91.2, C92.2, C94.2, C95.2, C96.2, IN11.3, IN11.14, J23.1, J24.6, OUT11.3, OUT11.14, PROC_PWR_EN11.2, R47.1, R48.1, U23.8, U23.PAD, U24.4, U24.9, U24.11, U24.12, U24.13, U24.14, U24.15
GND12: C97.2, C98.2, C99.2, C100.2, C102.2, C103.2, C104.2, IN12.3, IN12.14, J25.1, J26.6, OUT12.3, OUT12.14, PROC_PWR_EN12.2, R51.1, R52.1, U25.8, U25.PAD, U26.4, U26.9, U26.11, U26.12, U26.13, U26.14, U26.15
GND13: C105.2, C106.2, C107.2, C108.2, C110.2, C111.2, C112.2, IN13.3, IN13.14, J27.1, J28.6, OUT13.3, OUT13.14, PROC_PWR_EN13.2, R55.1, R56.1, U27.8, U27.PAD, U28.4, U28.9, U28.11, U28.12, U28.13, U28.14, U28.15
GND14: C113.2, C114.2, C115.2, C116.2, C118.2, C119.2, C120.2, IN14.3, IN14.14, J29.1, J30.6, OUT14.3, OUT14.14, PROC_PWR_EN14.2, R59.1, R60.1, U29.8, U29.PAD, U30.4, U30.9, U30.11, U30.12, U30.13, U30.14, U30.15
GND15: C121.2, C122.2, C123.2, C124.2, C126.2, C127.2, C128.2, IN15.3, IN15.14, J31.1, J32.6, OUT15.3, OUT15.14, PROC_PWR_EN15.2, R63.1, R64.1, U31.8, U31.PAD, U32.4, U32.9, U32.11, U32.12, U32.13, U32.14, U32.15
GND16: C129.2, C130.2, C131.2, C132.2, C134.2, C135.2, C136.2, IN16.3, IN16.14, J33.1, J34.6, OUT16.3, OUT16.14, PROC_PWR_EN16.2, R67.1, R68.1, U33.8, U33.PAD, U34.4, U34.9, U34.11, U34.12, U34.13, U34.14, U34.15
GND17: C137.2, C138.2, C139.2, C140.2, C142.2, C143.2, C144.2, IN17.3, IN17.14, J35.1, J36.6, OUT17.3, OUT17.14, PROC_PWR_EN17.2, R71.1, R72.1, U35.8, U35.PAD, U36.4, U36.9, U36.11, U36.12, U36.13, U36.14, U36.15
GND18: C145.2, C146.2, C147.2, C148.2, C150.2, C151.2, C152.2, IN18.3, IN18.14, J37.1, J38.6, OUT18.3, OUT18.14, PROC_PWR_EN18.2, R75.1, R76.1, U37.8, U37.PAD, U38.4, U38.9, U38.11, U38.12, U38.13, U38.14, U38.15
GND19: C153.2, C154.2, C155.2, C156.2, C158.2, C159.2, C160.2, IN19.3, IN19.14, J39.1, J40.6, OUT19.3, OUT19.14, PROC_PWR_EN19.2, R79.1, R80.1, U39.8, U39.PAD, U40.4, U40.9, U40.11, U40.12, U40.13, U40.14, U40.15
GND20: C161.2, C162.2, C163.2, C164.2, C166.2, C167.2, C168.2, IN20.3, IN20.14, J41.1, J42.6, OUT20.3, OUT20.14, PROC_PWR_EN20.2, R83.1, R84.1, U41.8, U41.PAD, U42.4, U42.9, U42.11, U42.12, U42.13, U42.14, U42.15
GND21: C169.2, C170.2, C171.2, C172.2, C174.2, C175.2, C176.2, IN21.3, IN21.14, J43.1, J44.6, OUT21.3, OUT21.14, PROC_PWR_EN21.2, R87.1, R88.1, U43.8, U43.PAD, U44.4, U44.9, U44.11, U44.12, U44.13, U44.14, U44.15
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
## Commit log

2021-05-18 Initial commit - ready for review
2021-05-24 Post-review updates
2021-05-25 Add VIN Max 5.5V
2021-05-26 Final tweaks
2021-05-27 Gapless production panel
2021-06-09 Update 16-way FPC Connector. Add missing PROD_IDs
2021-07-21 Add test firmware
2021-07-26 Add EEPROM_Test test sketch
2021-07-26 Adjust 1ms noIntDelay
2021-07-26 Work in progress
2021-07-26 Ready for initial tests - still work in progress
2021-07-27 Changes 'registers' to volatile. Restructure loop (process receive event). Rename register1V1.
2021-07-27 Adding WDT and sleep functionality
2021-07-28 Reduce current draw during sleep. Use wdt.h bit definitions.
2021-07-28 More power-down tweaks
2021-07-29 Add support for the smol Power Board LiPo
2021-08-02 Correcting I2C restart-after-power-down problems
2021-08-18 X02 - smol branding; L2 moved away from OUT connector
2021-08-19 Update smôl logo
2021-08-20 Change EZ to smôl on schematic
2021-09-28 Change .hex filename to 8.3 format
2021-10-28 Add SKU and product image
